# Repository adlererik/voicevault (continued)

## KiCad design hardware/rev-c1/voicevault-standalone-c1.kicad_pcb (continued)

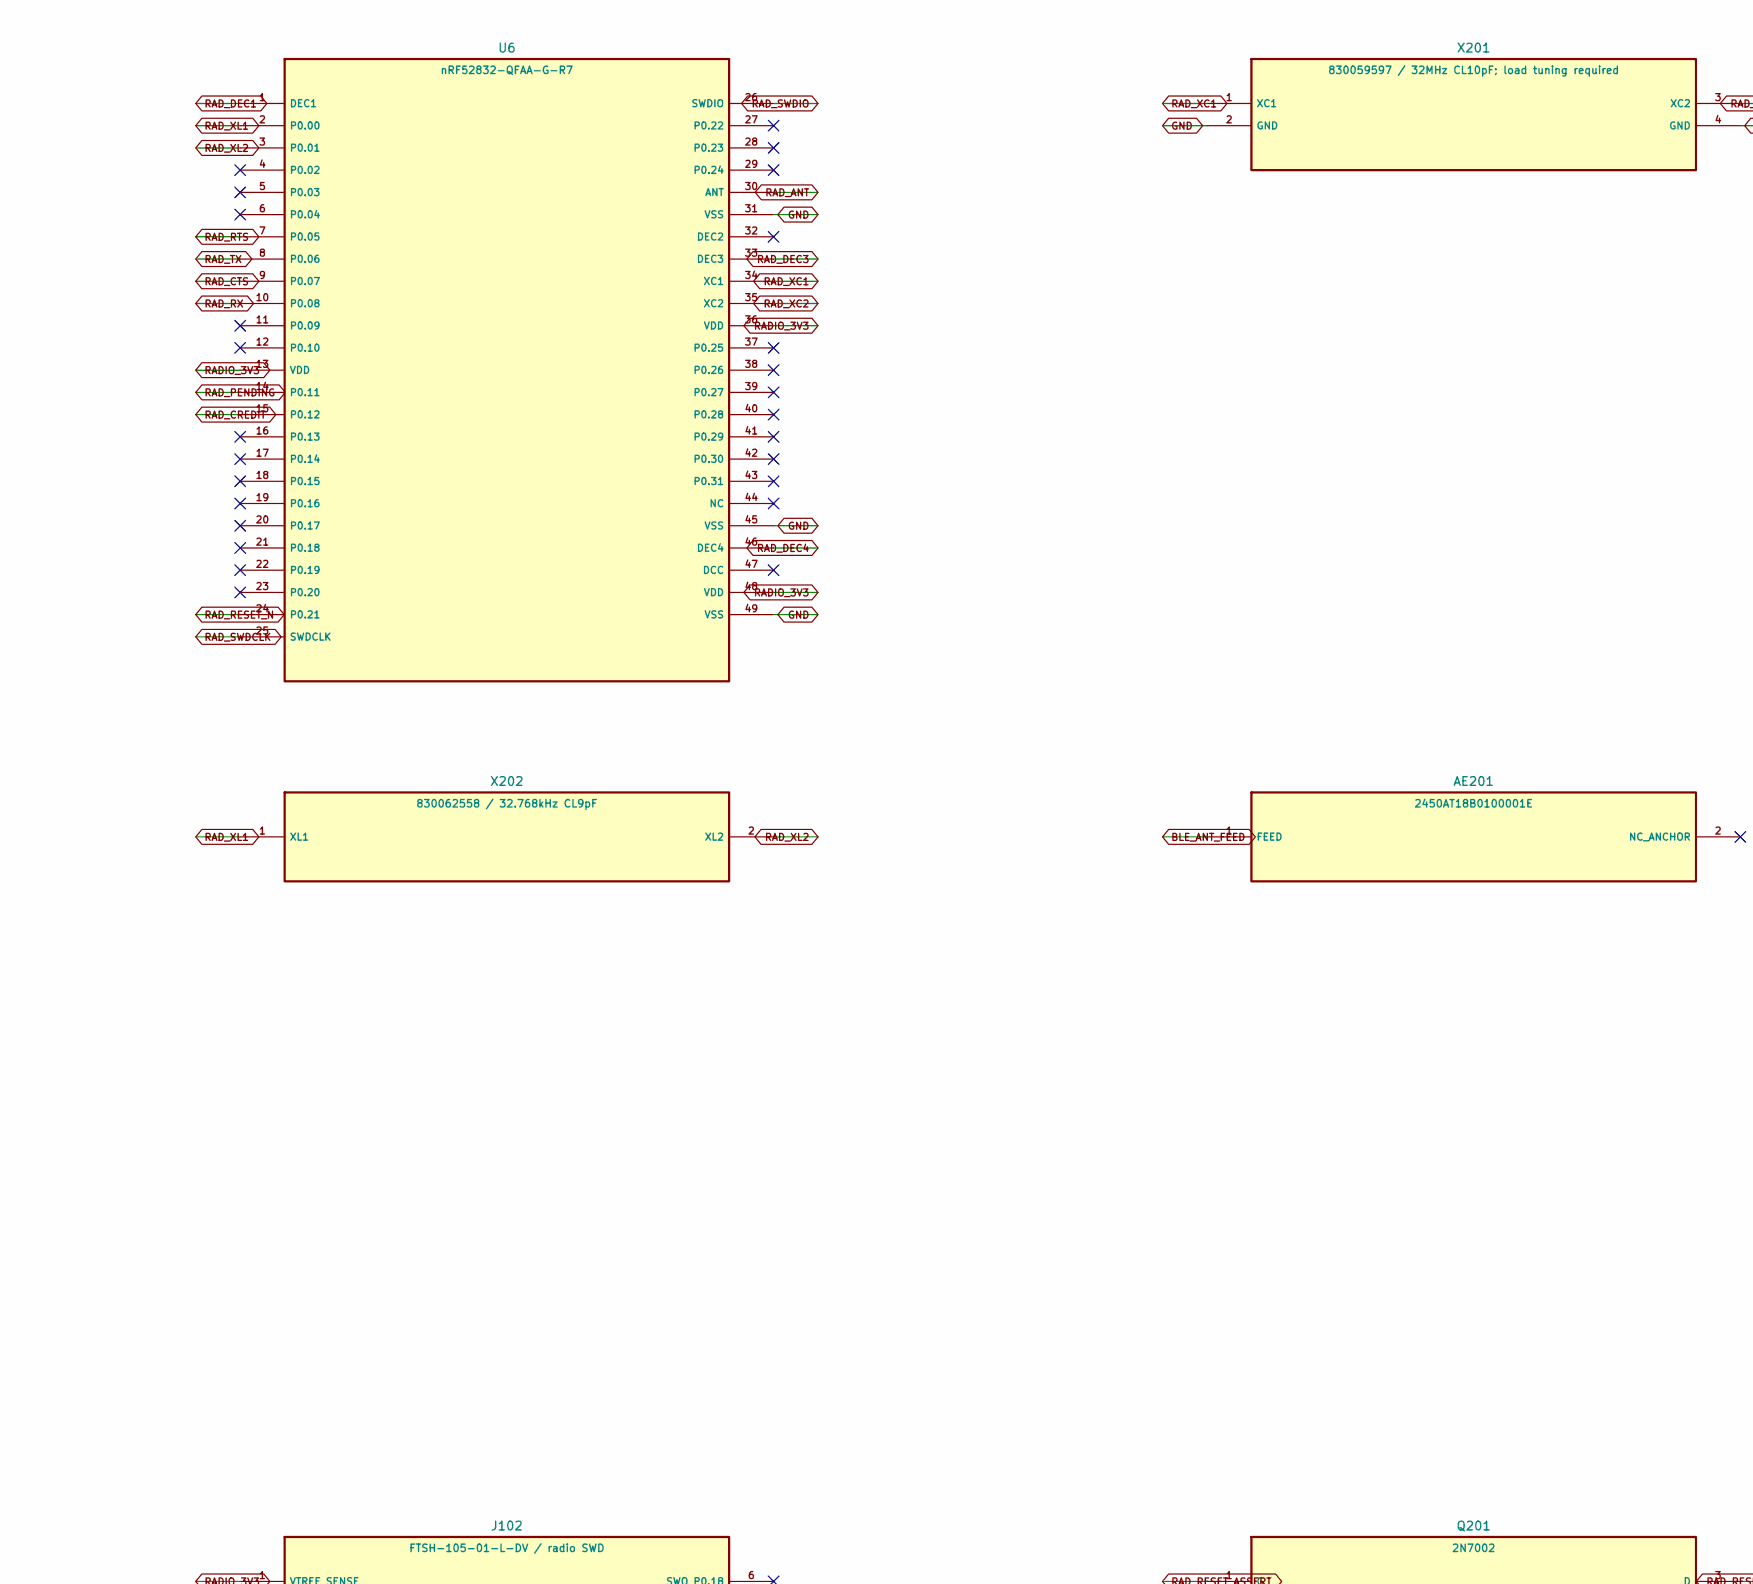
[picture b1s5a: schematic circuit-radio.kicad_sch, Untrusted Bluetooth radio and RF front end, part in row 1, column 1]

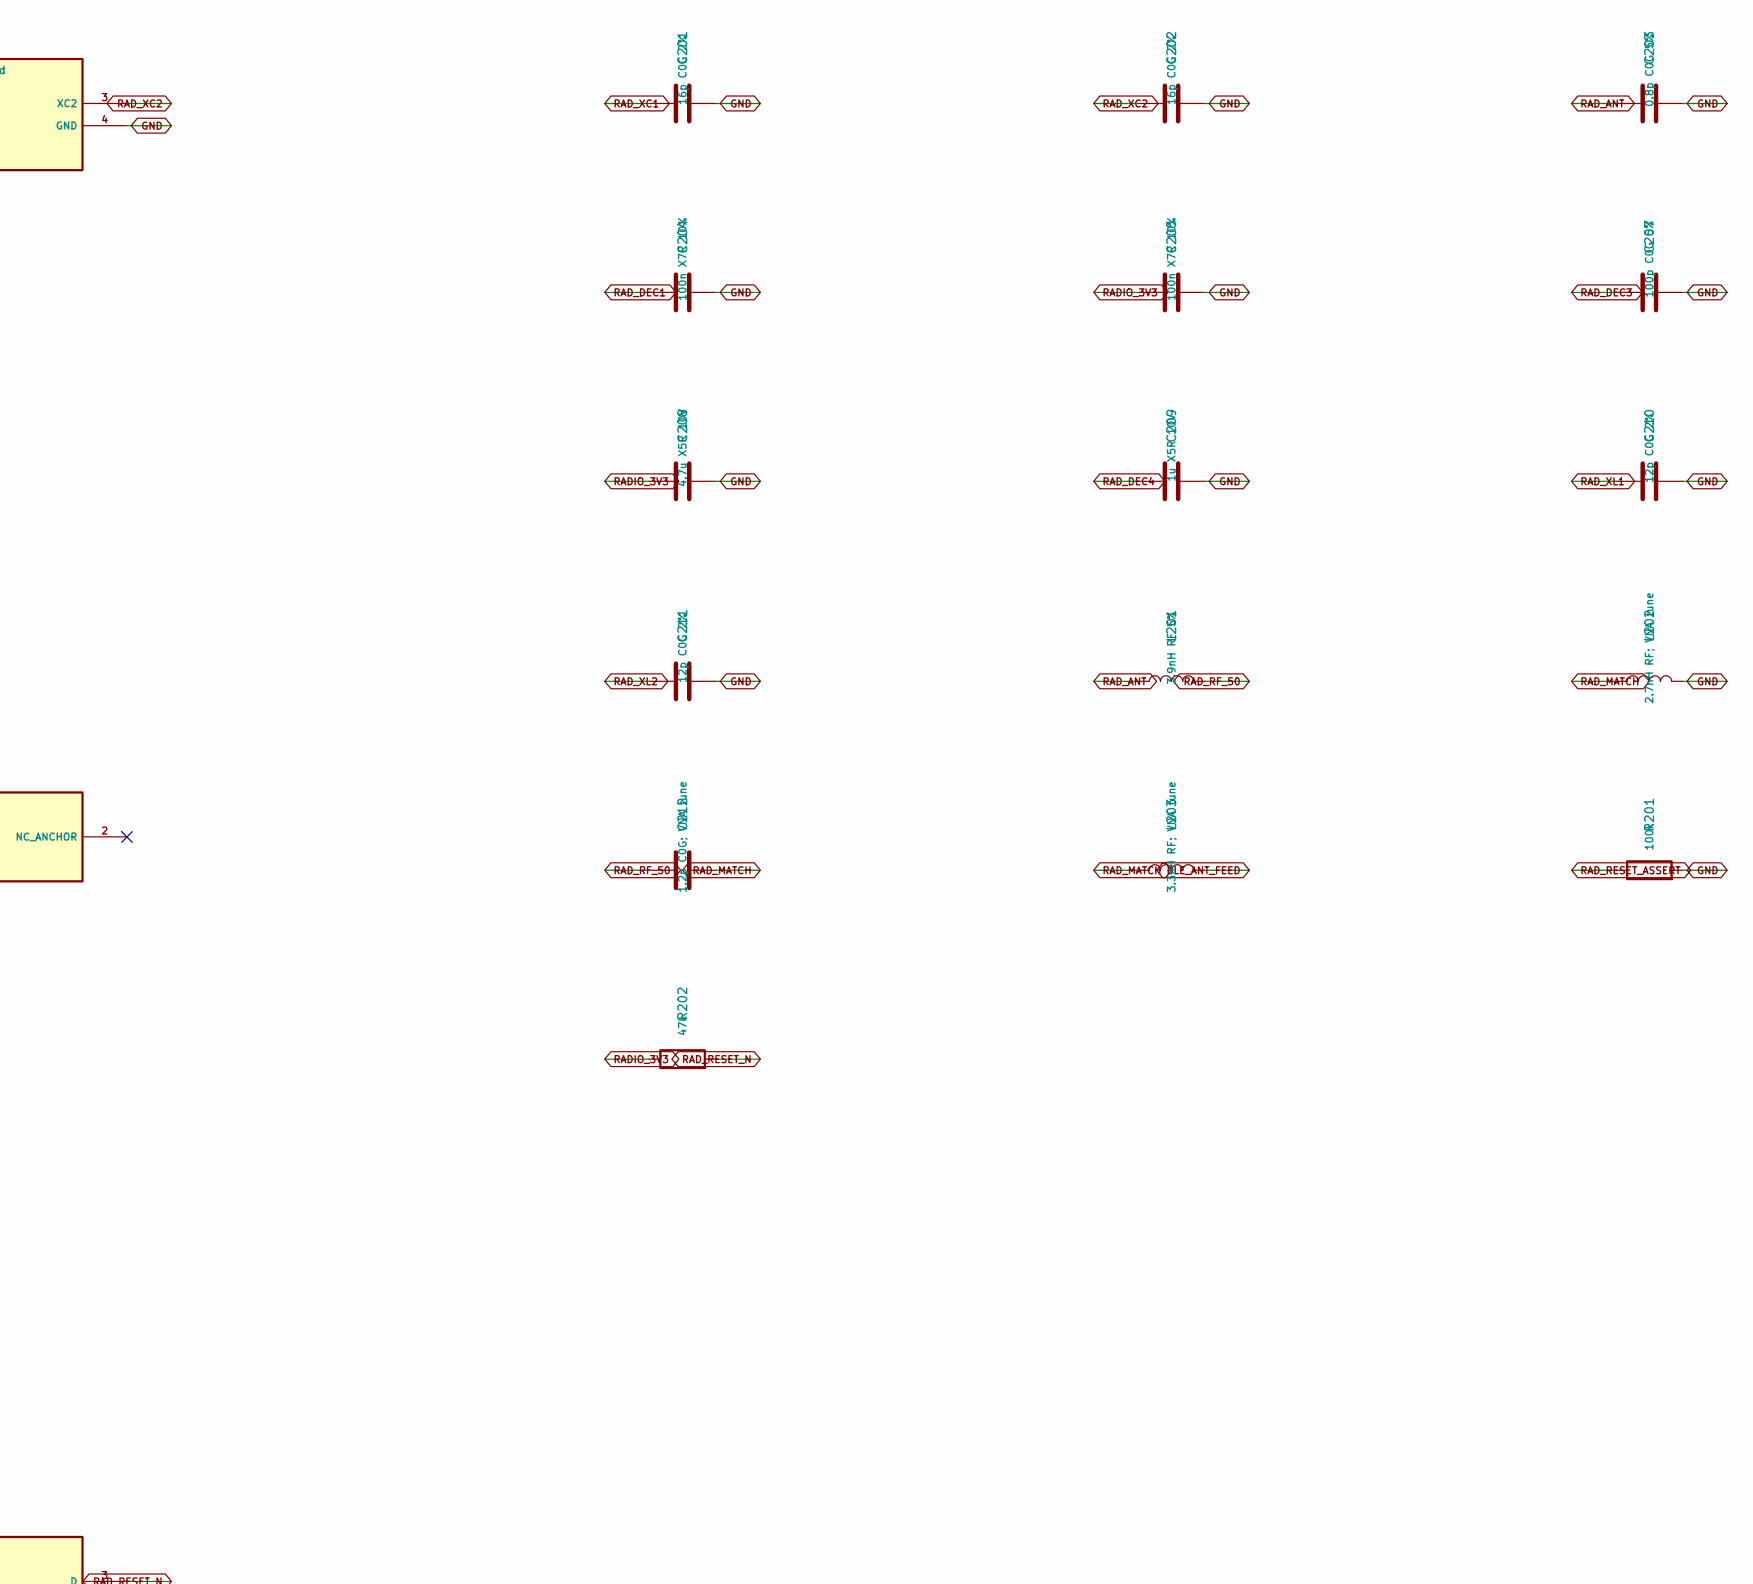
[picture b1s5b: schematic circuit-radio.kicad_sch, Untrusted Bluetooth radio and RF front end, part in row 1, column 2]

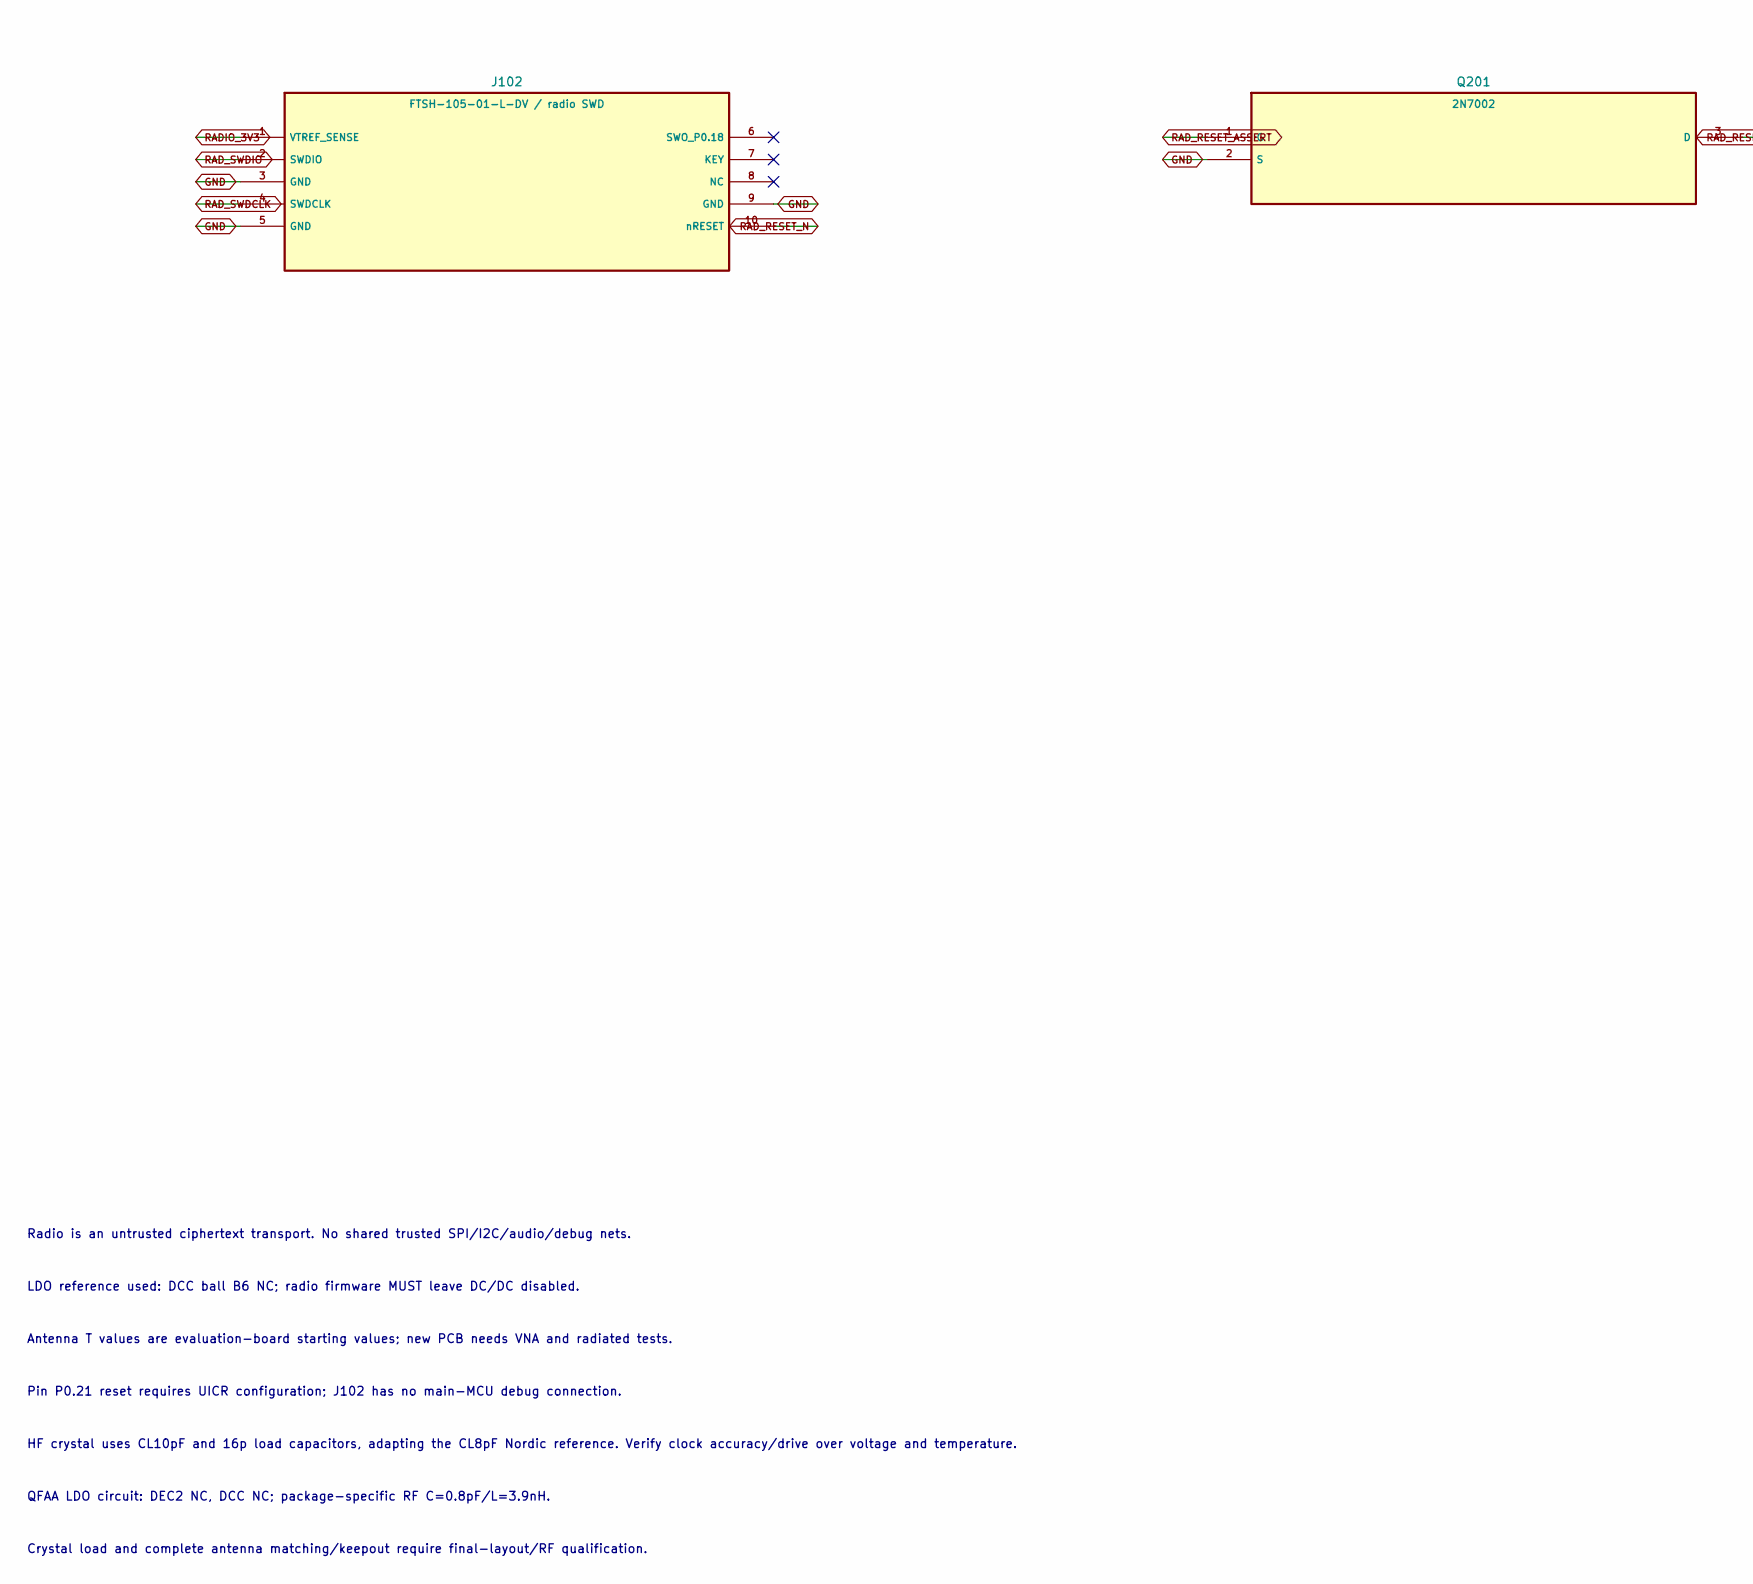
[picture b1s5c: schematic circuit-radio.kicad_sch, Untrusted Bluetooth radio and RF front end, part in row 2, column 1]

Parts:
AE201: 2450AT18B0100001E; Johanson_2450AT18x100
C201, C202: 16p C0G 2%; C_0201_0603Metric
C203: 0.8p C0G 5%; C_0402_1005Metric
C204, C205: 100n X7R 10%; C_0201_0603Metric
C207: 100p C0G 5%; C_0201_0603Metric
C208: 4.7u X5R 10V; C_0603_1608Metric
C209: 1u X5R 10V; C_0402_1005Metric
C210, C211: 12p C0G 2%; C_0201_0603Metric
C212: 1.2p C0G; VNA tune; C_0402_1005Metric
J102: FTSH-105-01-L-DV / radio SWD; Samtec_FTSH-105-01-L-DV
L201: 3.9nH RF 5%; L_0402_1005Metric
L202: 2.7nH RF; VNA tune; L_0402_1005Metric
L203: 3.3nH RF; VNA tune; L_0402_1005Metric
Q201: 2N7002; SOT-23
R201: 100k; R_0402_1005Metric
R202: 47k; R_0402_1005Metric
U6: nRF52832-QFAA-G-R7; QFN-48-1EP_6x6mm_P0.4mm_EP4.66x4.66mm
X201: 830059597 / 32MHz CL10pF; load tuning required; Crystal_SMD_2016-4Pin_2.0x1.6mm
X202: 830062558 / 32.768kHz CL9pF; Crystal_SMD_2012-2Pin_2.0x1.2mm

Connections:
BLE_ANT_FEED: AE201.1 (FEED), L203.2
GND: C201.2, C202.2, C203.2, C204.2, C205.2, C207.2, C208.2, C209.2, C210.2, C211.2, J102.3 (GND), J102.5 (GND), J102.9 (GND), L202.2, Q201.2 (S), R201.2, U6.31 (VSS), U6.45 (VSS), U6.49 (VSS), X201.2 (GND), X201.4 (GND); also elsewhere on the board
RADIO_3V3: C205.1, C208.1, J102.1 (VTREF_SENSE), R202.1, U6.13 (VDD), U6.36 (VDD), U6.48 (VDD); also elsewhere on the board
RAD_ANT: C203.1, L201.1, U6.30 (ANT)
RAD_CREDIT: U6.15 (P0.12); also elsewhere on the board
RAD_CTS: U6.9 (P0.07); also elsewhere on the board
RAD_DEC1: C204.1, U6.1 (DEC1)
RAD_DEC3: C207.1, U6.33 (DEC3)
RAD_DEC4: C209.1, U6.46 (DEC4)
RAD_MATCH: C212.2, L202.1, L203.1
RAD_PENDING: U6.14 (P0.11); also elsewhere on the board
RAD_RESET_ASSERT: Q201.1 (G), R201.1; also elsewhere on the board
RAD_RESET_N: J102.10 (nRESET), Q201.3 (D), R202.2, U6.24 (P0.21)
RAD_RF_50: C212.1, L201.2
RAD_RTS: U6.7 (P0.05); also elsewhere on the board
RAD_RX: U6.10 (P0.08); also elsewhere on the board
RAD_SWDCLK: J102.4 (SWDCLK), U6.25 (SWDCLK)
RAD_SWDIO: J102.2 (SWDIO), U6.26 (SWDIO)
RAD_TX: U6.8 (P0.06); also elsewhere on the board
RAD_XC1: C201.1, U6.34 (XC1), X201.1 (XC1)
RAD_XC2: C202.1, U6.35 (XC2), X201.3 (XC2)
RAD_XL1: C210.1, U6.2 (P0.00), X202.1 (XL1)
RAD_XL2: C211.1, U6.3 (P0.01), X202.2 (XL2)

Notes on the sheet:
Radio is an untrusted ciphertext transport. No shared trusted SPI/I2C/audio/debug nets.
LDO reference used: DCC ball B6 NC; radio firmware MUST leave DC/DC disabled.
Antenna T values are evaluation-board starting values; new PCB needs VNA and radiated tests.
Pin P0.21 reset requires UICR configuration; J102 has no main-MCU debug connection.
HF crystal uses CL10pF and 16p load capacitors, adapting the CL8pF Nordic reference. Verify clock accuracy/drive over voltage and temperature.
QFAA LDO circuit: DEC2 NC, DCC NC; package-specific RF C=0.8pF/L=3.9nH.
Crystal load and complete antenna matching/keepout require final-layout/RF qualification.

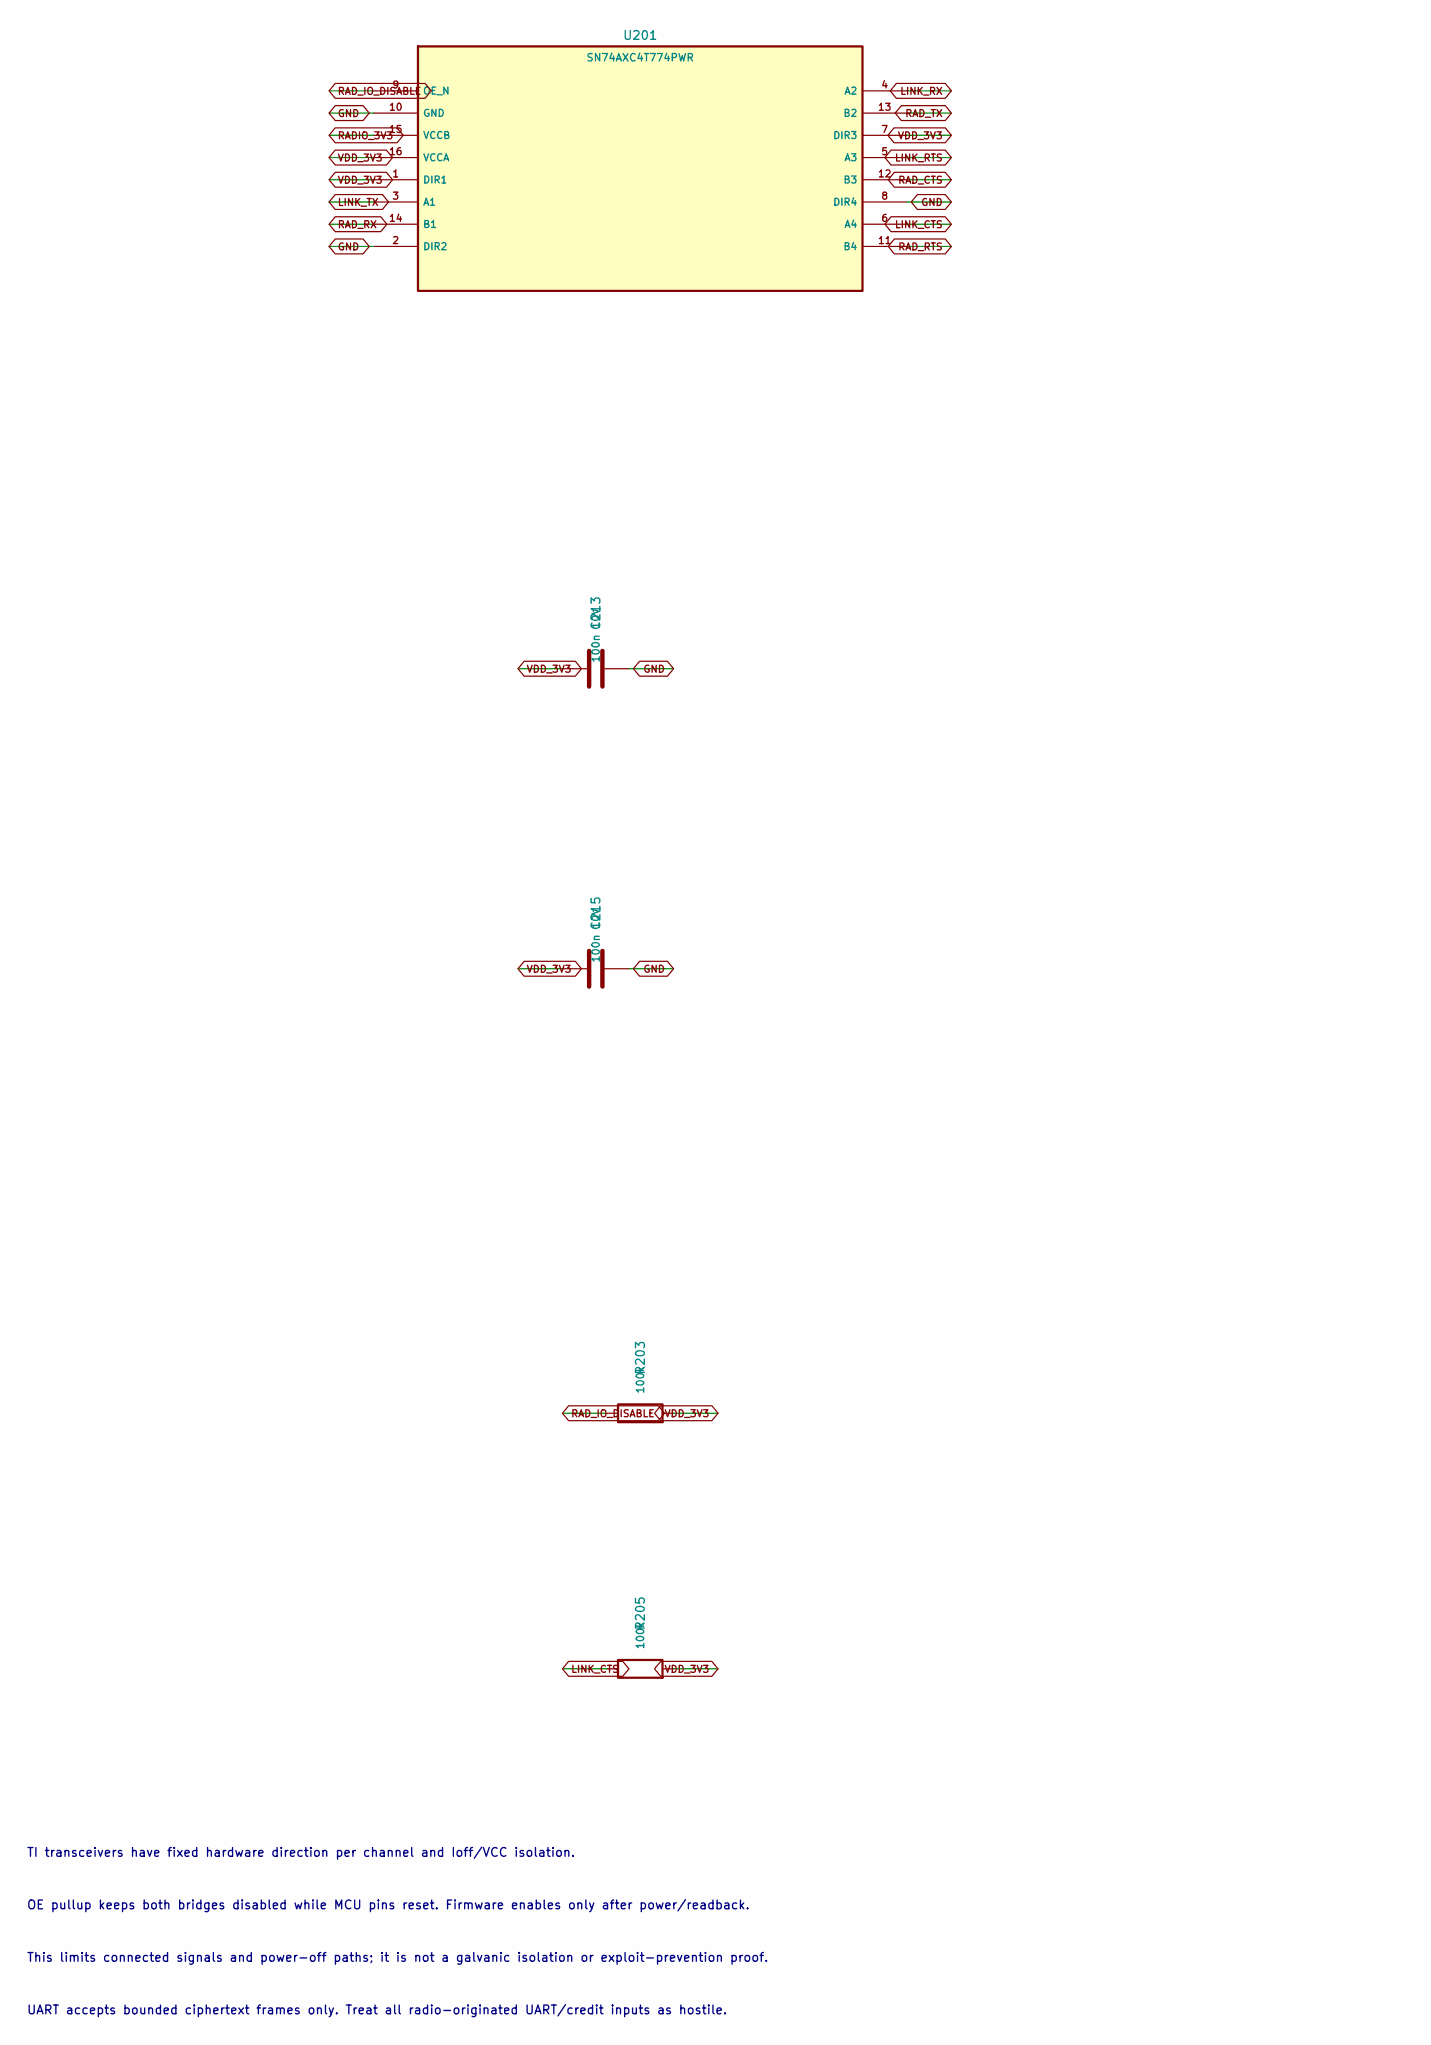
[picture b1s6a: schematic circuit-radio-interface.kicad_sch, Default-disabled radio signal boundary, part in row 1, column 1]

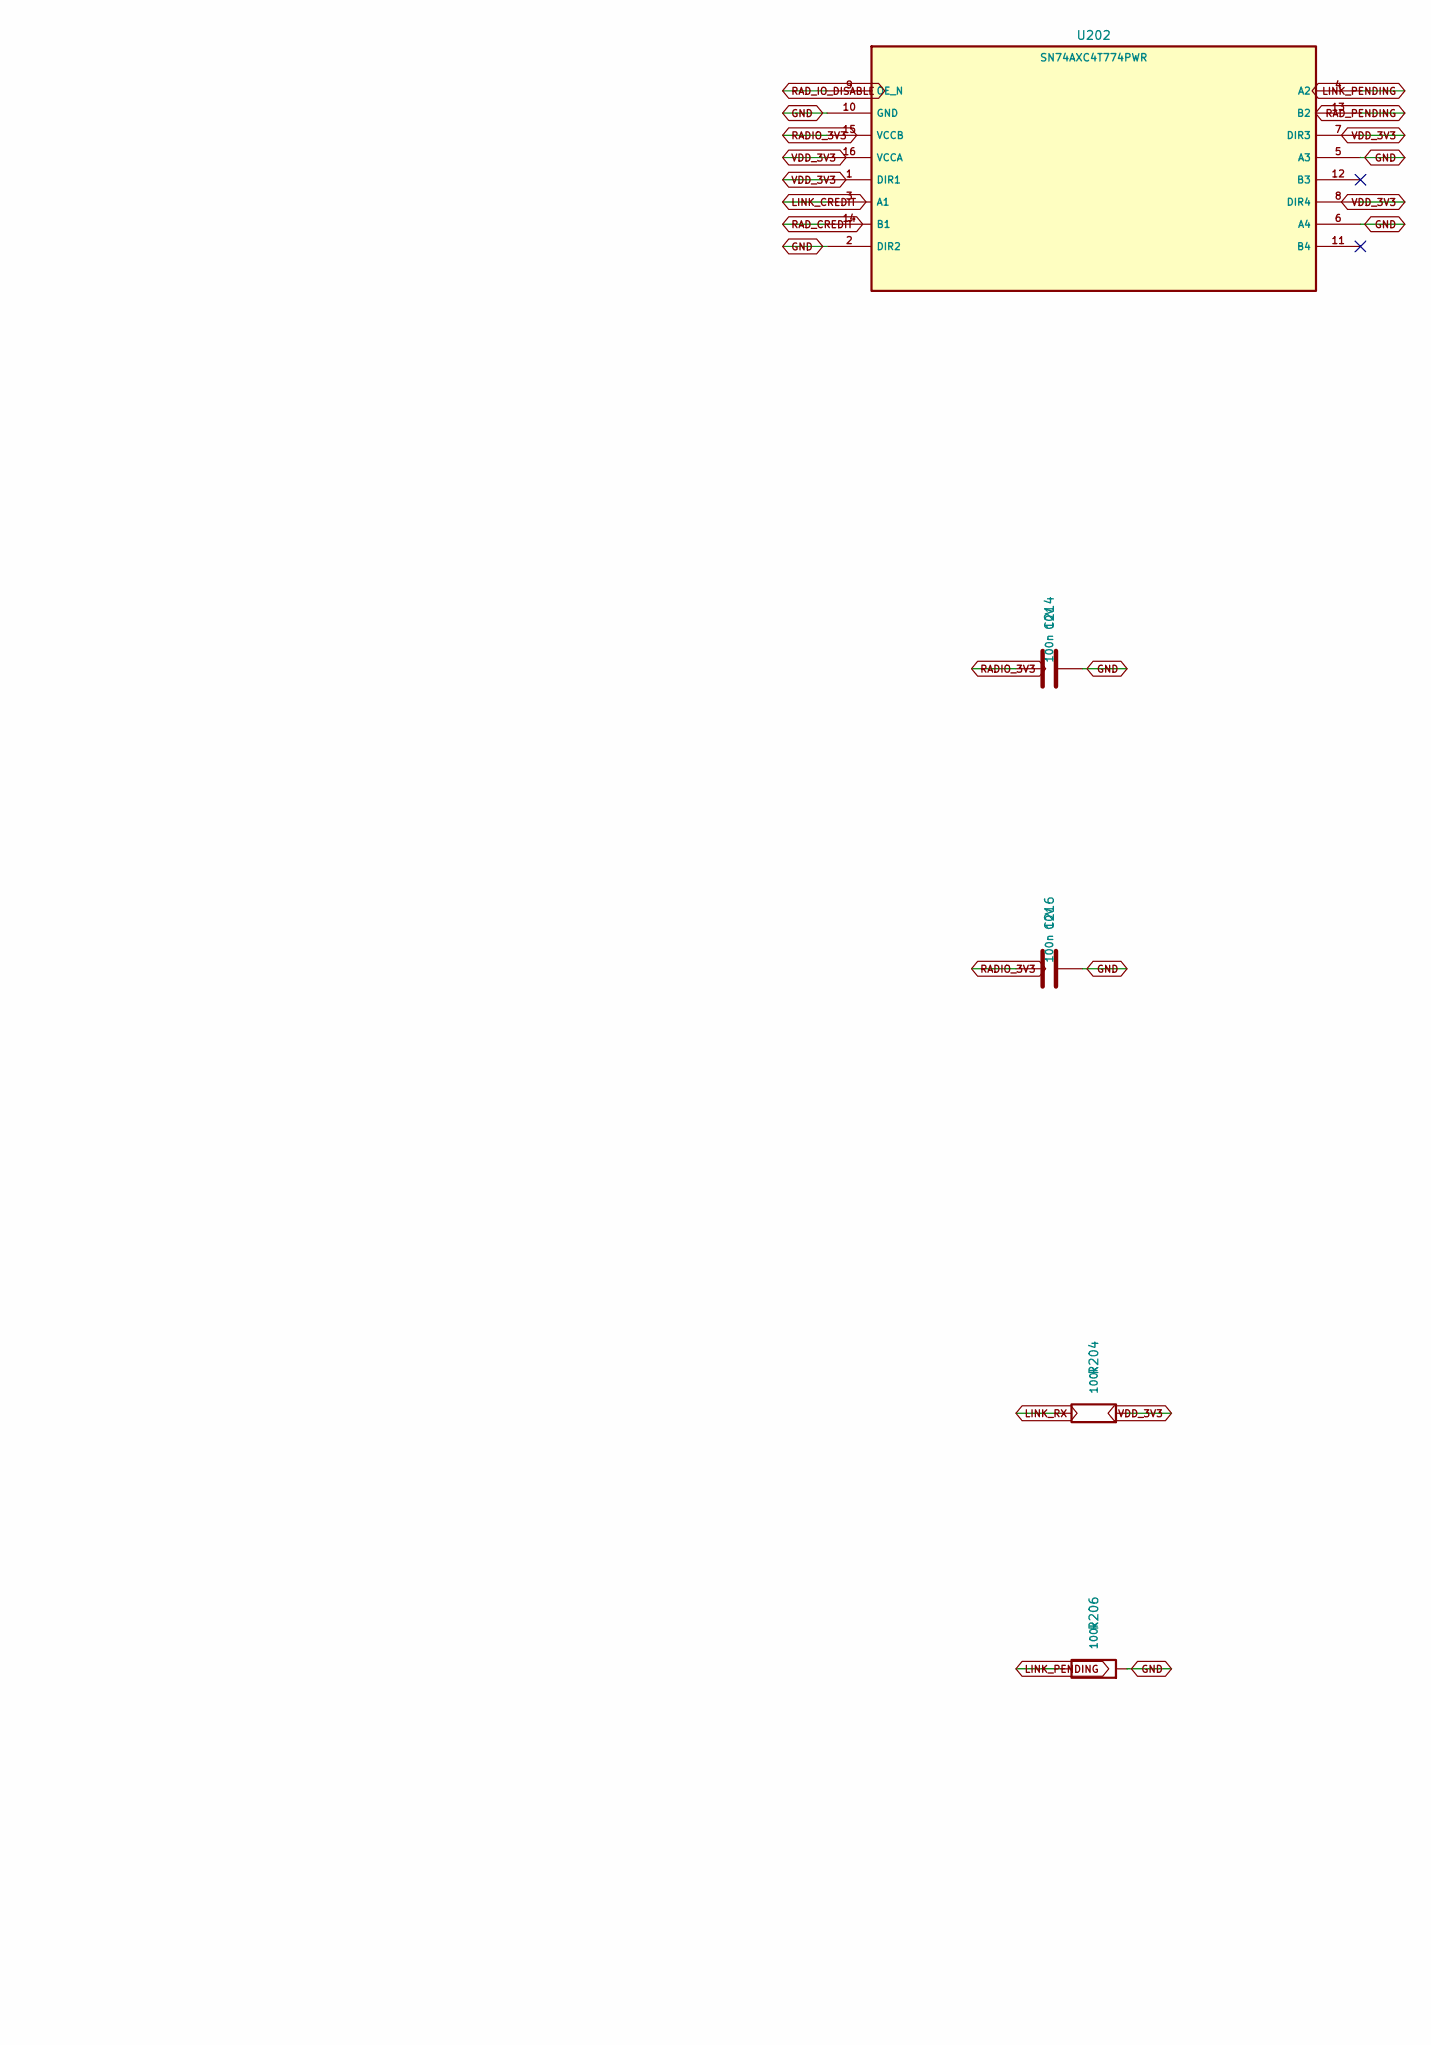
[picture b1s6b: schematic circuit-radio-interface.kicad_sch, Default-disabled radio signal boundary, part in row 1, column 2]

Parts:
C213, C214, C215, C216: 100n 10V; C_0402_1005Metric
R203, R204, R205, R206: 100k; R_0402_1005Metric
U201, U202: SN74AXC4T774PWR; TSSOP-16_4.4x5mm_P0.65mm

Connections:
GND: C213.2, C214.2, C215.2, C216.2, R206.2, U201.2 (DIR2), U201.8 (DIR4), U201.10 (GND), U202.2 (DIR2), U202.5 (A3), U202.6 (A4), U202.10 (GND); also elsewhere on the board
LINK_CREDIT: U202.3 (A1); also elsewhere on the board
LINK_CTS: R205.1, U201.6 (A4); also elsewhere on the board
LINK_PENDING: R206.1, U202.4 (A2); also elsewhere on the board
LINK_RTS: U201.5 (A3); also elsewhere on the board
LINK_RX: R204.1, U201.4 (A2); also elsewhere on the board
LINK_TX: U201.3 (A1); also elsewhere on the board
RADIO_3V3: C214.1, C216.1, U201.15 (VCCB), U202.15 (VCCB); also elsewhere on the board
RAD_CREDIT: U202.14 (B1); also elsewhere on the board
RAD_CTS: U201.12 (B3); also elsewhere on the board
RAD_IO_DISABLE: R203.1, U201.9 (OE_N), U202.9 (OE_N); also elsewhere on the board
RAD_PENDING: U202.13 (B2); also elsewhere on the board
RAD_RTS: U201.11 (B4); also elsewhere on the board
RAD_RX: U201.14 (B1); also elsewhere on the board
RAD_TX: U201.13 (B2); also elsewhere on the board
VDD_3V3: C213.1, C215.1, R203.2, R204.2, R205.2, U201.1 (DIR1), U201.7 (DIR3), U201.16 (VCCA), U202.1 (DIR1), U202.7 (DIR3), U202.8 (DIR4), U202.16 (VCCA); also elsewhere on the board

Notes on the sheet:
TI transceivers have fixed hardware direction per channel and Ioff/VCC isolation.
OE pullup keeps both bridges disabled while MCU pins reset. Firmware enables only after power/readback.
This limits connected signals and power-off paths; it is not a galvanic isolation or exploit-prevention proof.
UART accepts bounded ciphertext frames only. Treat all radio-originated UART/credit inputs as hostile.
